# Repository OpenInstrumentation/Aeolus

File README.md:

# Aeolus
A multi-height anemometer for measuring wind speed and direction over a vertical gradient.

CC-BY-SA 2019, P. Marchetto, S. Vandycke, and D. J. Heuschele

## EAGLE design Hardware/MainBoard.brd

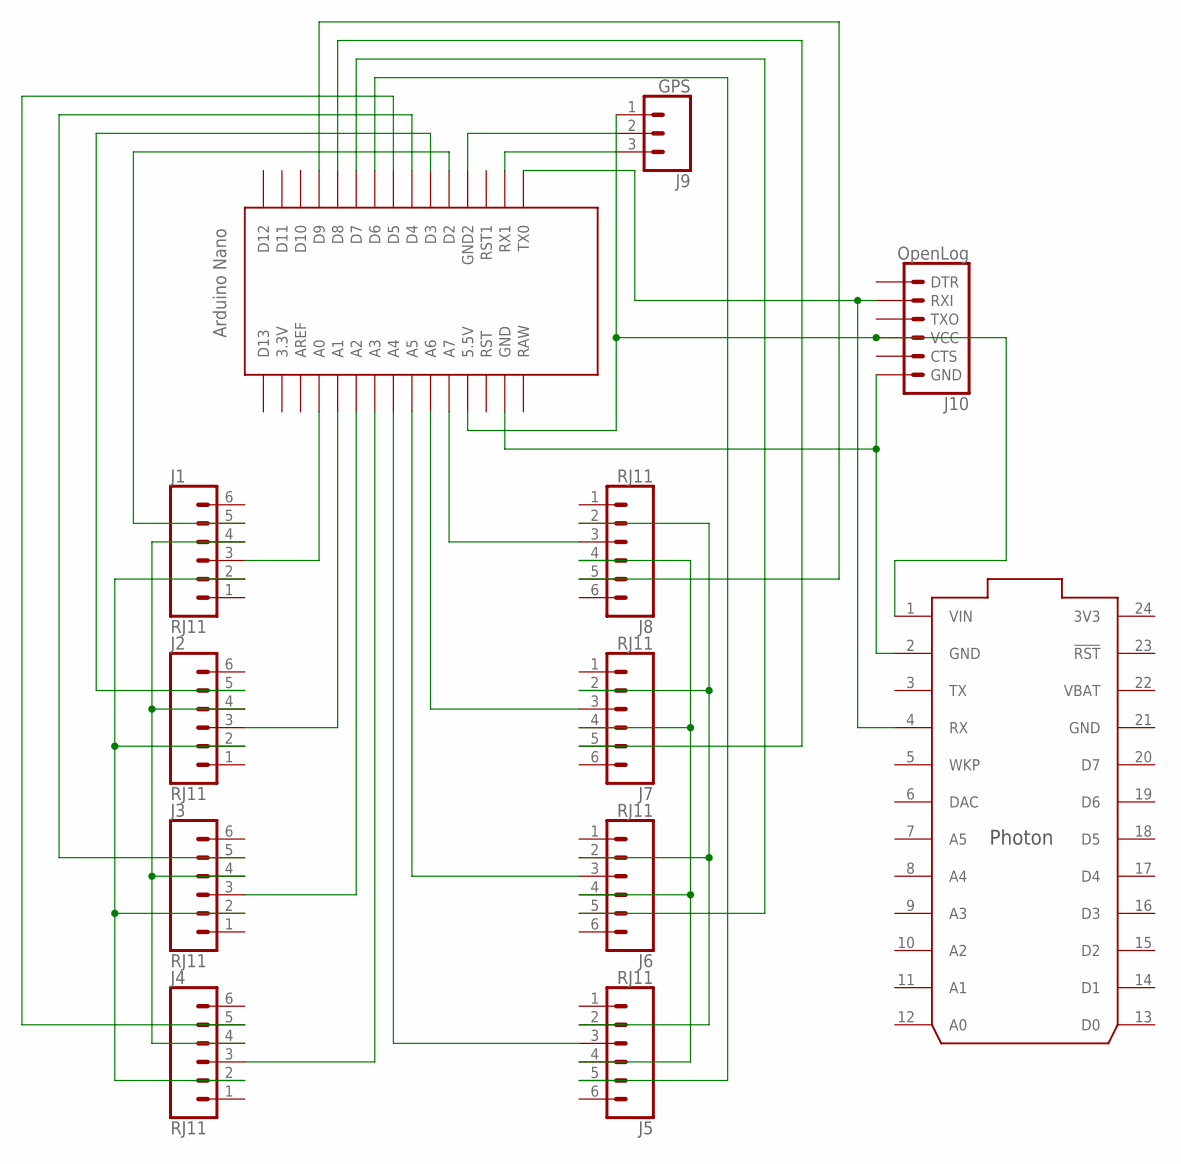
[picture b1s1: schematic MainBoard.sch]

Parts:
J1, J2, J3, J4, J5, J6, J7, J8: RJ11; RJ11-6
J9: GPS; 1X03
J10: OpenLog; 1X06
U$1: NANO
U$2: PHOTON_WITH_HEADERS; PHOTON

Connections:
3V3: U$2.24 (3V3)
GND: U$2.21 (GND)
unnamed: J1.2, J2.2, J3.2, J4.2
unnamed: J1.3, U$1.A0
unnamed: J2.3, U$1.A1
unnamed: J5.2, J6.2, J7.2, J8.2
unnamed: J1.4, J2.4, J3.4, J4.4
unnamed: J5.4, J6.4, J7.4, J8.4
unnamed: J3.3, U$1.A2
unnamed: J4.3, U$1.A3
unnamed: J5.3, U$1.A4
unnamed: J6.3, U$1.A5
unnamed: J7.3, U$1.A6
unnamed: J8.3, U$1.A7
unnamed: J1.5, U$1.D2
unnamed: J2.5, U$1.D3
unnamed: J3.5, U$1.D4
unnamed: J4.5, U$1.D5
unnamed: J5.5, U$1.D6
unnamed: J6.5, U$1.D7
unnamed: J7.5, U$1.D8
unnamed: J8.5, U$1.D9
unnamed: J9.3, U$1.RX1
unnamed: J9.2, U$1.GND1 (GND2)
unnamed: J9.1, J10.4 (VCC), U$1.5V (5.5V), U$2.1 (VIN)
unnamed: J10.6 (GND), U$1.GND, U$2.2 (GND)
unnamed: J10.2 (RXI), U$1.TX0, U$2.4 (RX)
VBAT: U$2.22 (VBAT)

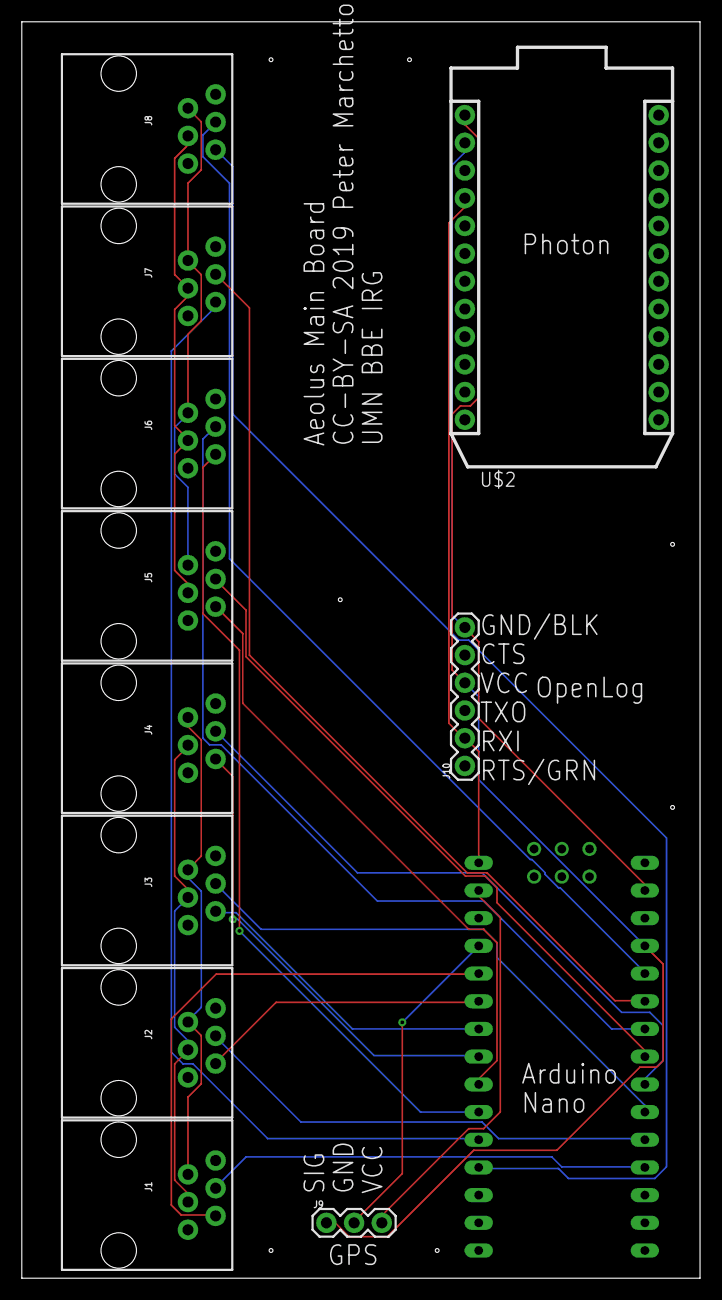
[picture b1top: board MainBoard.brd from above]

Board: 2 copper layers, 62.2 x 115.2 mm, 12 parts (0 on the bottom side), 25 nets.

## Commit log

2019-01-30 Fixed space

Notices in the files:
Hardware/MainBoard.brd:
CC-BY-SA 2019 Peter Marchetto
parts and their libraries:
SparkFun-Connectors: Licensing: Creative Commons ShareAlike 4.0 International - https://creativecommons.org/licenses/by-sa/4.0
Particle-Devices: Licensing: Designed by Particle.
